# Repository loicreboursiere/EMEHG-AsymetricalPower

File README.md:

# EMEHG-AsymetricalPower

Hexaphonic guitars using 13 pin DIN connectors are genarally based on Roland systems which need asymetrical powering. Once you use a setup that doesn't involve Roland devices, you need to have somewhere in your setup an asymetrical power unit.
This repository gathers different approaches to this problem.

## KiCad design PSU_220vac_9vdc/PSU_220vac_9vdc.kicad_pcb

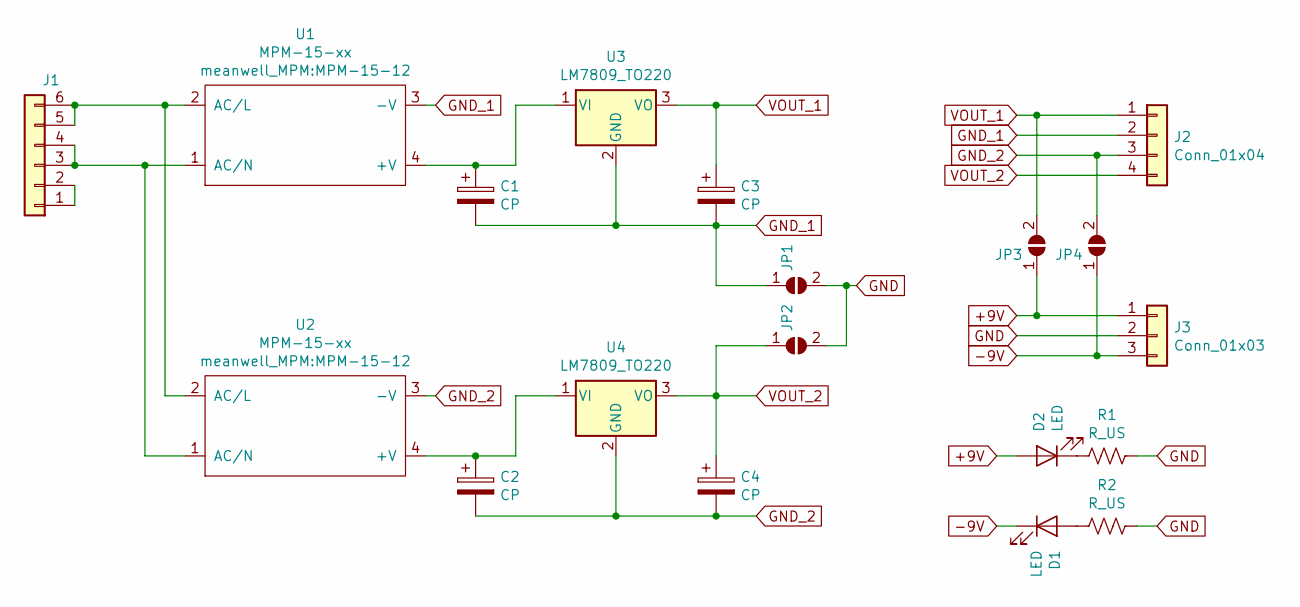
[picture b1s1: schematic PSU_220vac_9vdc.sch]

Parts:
C1, C2, C3, C4: CP; CP_Radial_D5.0mm_P2.50mm
D1, D2: LED; LED_D3.0mm
J1: Conn_01x05; TerminalBlock_bornier-6_P5.08mm
J2: Conn_01x04; Molex_KK-254_AE-6410-04A_1x04_P2.54mm_Vertical
J3: Conn_01x03; Molex_KK-254_AE-6410-03A_1x03_P2.54mm_Vertical
JP1, JP2, JP3, JP4: SolderJumper_2_Open; SolderJumper-2_P1.3mm_Open_RoundedPad1.0x1.5mm
R1, R2: R_US; R_Axial_DIN0207_L6.3mm_D2.5mm_P7.62mm_Horizontal
U1, U2: MPM-15-xx; MPM-15-12
U3, U4: LM7809_TO220; Heatsink_TO-220

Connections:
+9V: D2.2 (A), J3.1, JP3.1 (A)
-9V: D1.1 (K), J3.3, JP4.1 (A)
GND: J3.2, JP1.2 (B), JP2.2 (B), R1.2, R2.1
GND_1: C1.2, C3.2, J2.2, JP1.1 (A), U1.3 (-V), U3.2 (GND)
GND_2: C2.2, C4.2, J2.3, JP4.2 (B), U2.3 (-V), U4.2 (GND)
unnamed: C1.1, U1.4 (+V), U3.1 (VI)
unnamed: C2.1, U2.4 (+V), U4.1 (VI)
unnamed: D1.2 (A), R2.2
unnamed: D2.1 (K), R1.1
unnamed: J1.1, J1.2
unnamed: J1.3, J1.4, U1.1 (AC/N), U2.1 (AC/N)
unnamed: J1.5, J1.6, U1.2 (AC/L), U2.2 (AC/L)
VOUT_1: C3.1, J2.1, JP3.2 (B), U3.3 (VO)
VOUT_2: C4.1, J2.4, JP2.1 (A), U4.3 (VO)

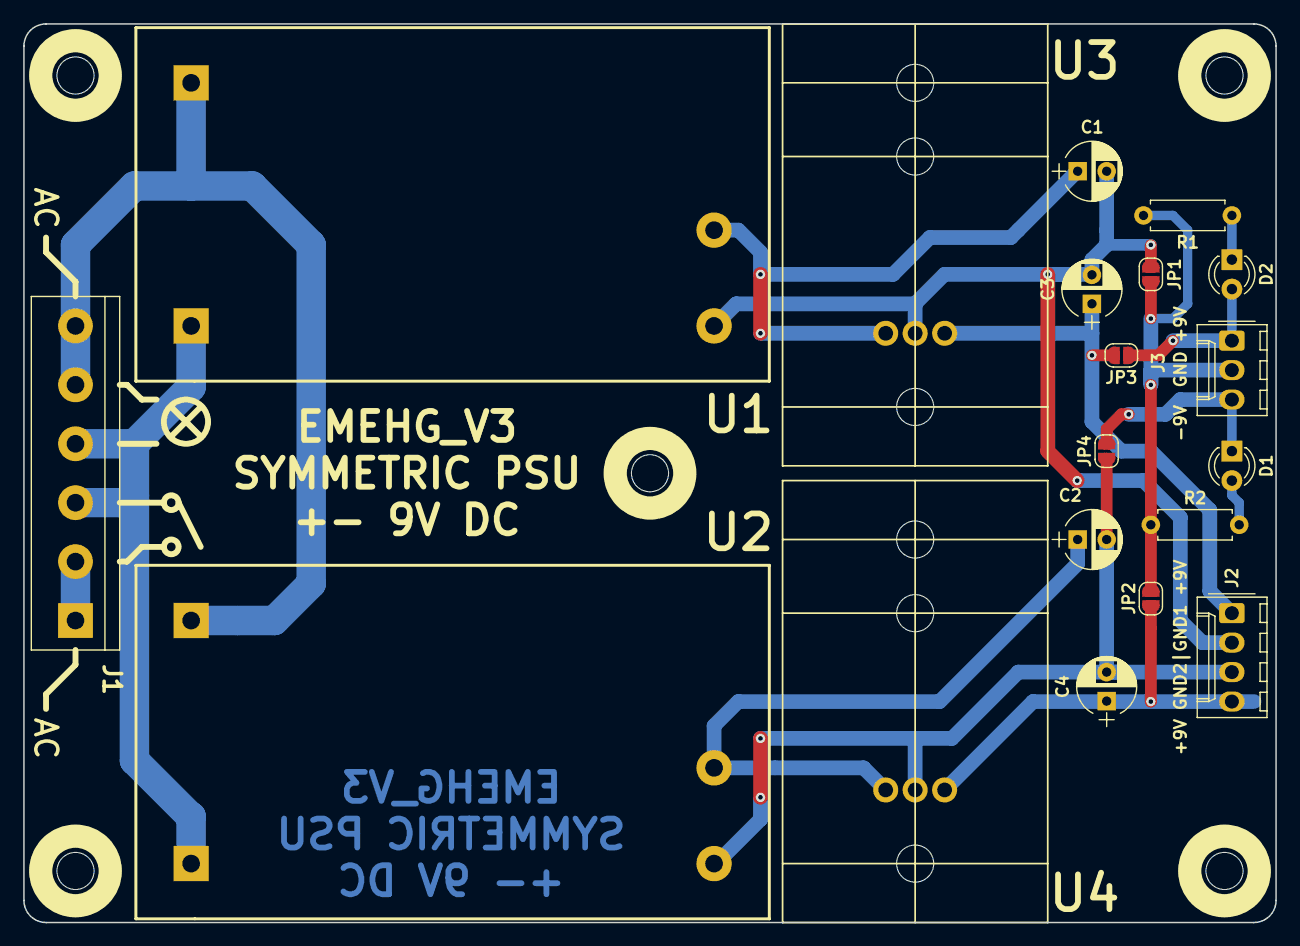
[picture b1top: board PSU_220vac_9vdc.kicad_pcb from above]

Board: 2 copper layers, 108.0 x 77.5 mm, 19 parts (0 on the bottom side), 14 nets.

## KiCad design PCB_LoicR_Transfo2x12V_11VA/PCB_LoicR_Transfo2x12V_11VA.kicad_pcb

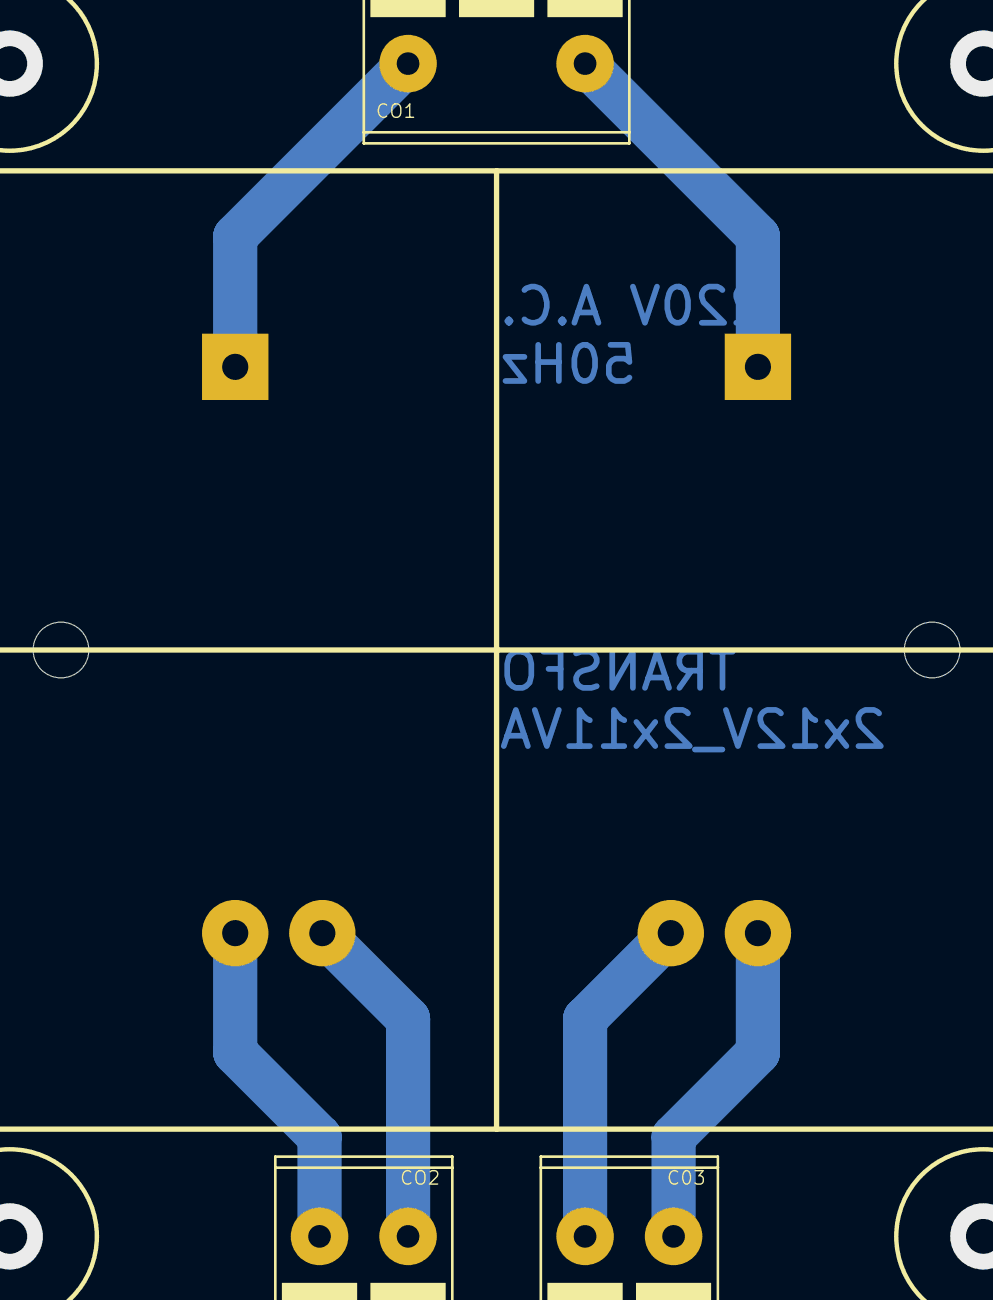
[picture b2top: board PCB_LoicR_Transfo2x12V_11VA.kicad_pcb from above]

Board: 2 copper layers, 4 parts (0 on the bottom side), 6 nets.

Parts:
C03: MKDS02
CO1: MKDS03-1
CO2: MKDS02
E$1: MYRRA_2X12V_11VA

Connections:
S$3: CO1.1, E$1.P$2
S$6: CO1.3, E$1.P$1
S$7: CO2.1, E$1.P$6
S$9: CO2.2, E$1.P$5
S$10: C03.2, E$1.P$4
S$11: C03.1, E$1.P$3

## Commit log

2021-07-26 Asymetrical power for hex pickup v1
2021-08-02 The different versions
